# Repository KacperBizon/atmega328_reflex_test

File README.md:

# reflex test

### How to use
- You win by pressing the button on your side faster than your opponent
- To go to the next round press any button for 1s
- Singleplayer - the game finishes with first keypress, multiplayer - both players need to press the keys to finish round 
### Components
- R1 - 10K
- R2-R11 - recommended 3.3k-6.8k
- C1,C2 - 22pF
- C3,C4,C5 - 100nF
- C6 - 10uF

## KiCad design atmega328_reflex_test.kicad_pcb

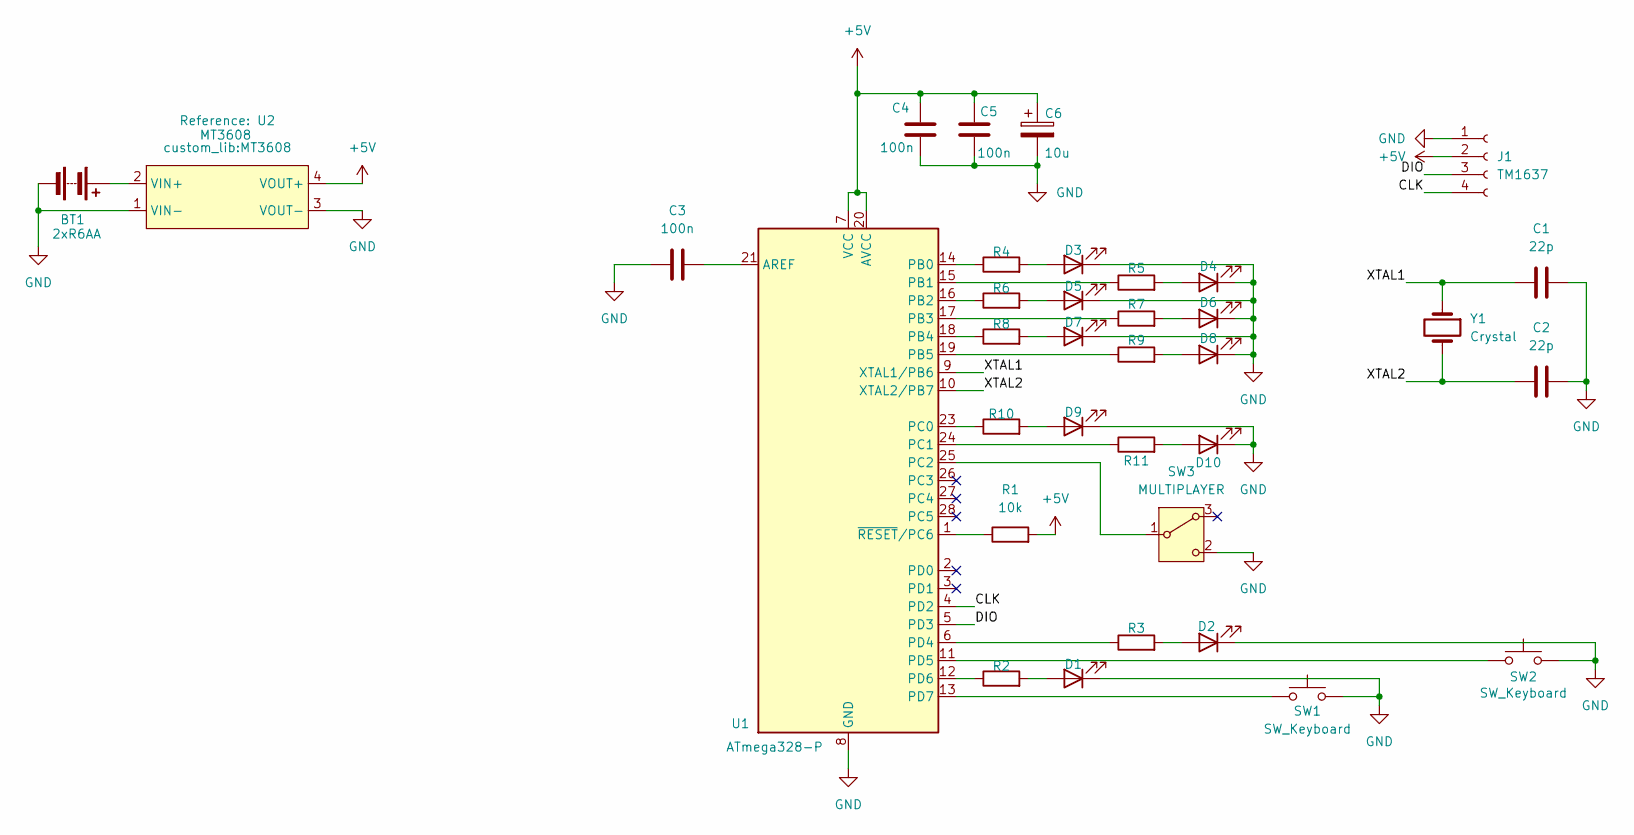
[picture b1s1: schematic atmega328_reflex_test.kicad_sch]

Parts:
BT1: 2xR6AA; 2xAA_holder
C1, C2: 22p; C_Disc_D3.0mm_W1.6mm_P2.50mm
C3, C4, C5: 100n; C_Disc_D4.3mm_W1.9mm_P5.00mm
C6: 10u; CP_Radial_D8.0mm_P3.80mm
D1, D2: LED; LED_D5.0mm
D3, D4, D5, D6, D7, D8, D9, D10: LED; LED_D3.0mm
J1: TM1637; HW069
R1: 10k; R_Axial_DIN0207_L6.3mm_D2.5mm_P7.62mm_Horizontal
R2, R3: 3k3; R_Axial_DIN0207_L6.3mm_D2.5mm_P7.62mm_Horizontal
R4, R5, R6, R7, R8, R9, R10, R11: 5k1; R_Axial_DIN0207_L6.3mm_D2.5mm_P7.62mm_Horizontal
SW1, SW2: SW_Keyboard; SW_Cherry_MX_1.00u_PCB
SW3: MULTIPLAYER; SW_Slide_8.6x3.8x7.0_P2.54mm
U1: ATmega328-P; DIP-28_W7.62mm
U2: MT3608
Y1: Crystal; Crystal_HC49-4H_Vertical

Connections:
+5V: C4.2, C5.2, C6.1, J1.2, R1.2, U1.7 (VCC), U1.20 (AVCC), U2.4 (VOUT+)
/CLK: J1.4, U1.4 (PD2)
/DIO: J1.3, U1.5 (PD3)
/XTAL1: C1.1, U1.9 (XTAL1/PB6), Y1.1
/XTAL2: C2.1, U1.10 (XTAL2/PB7), Y1.2
GND: BT1.2 (-), C1.2, C2.2, C3.1, C4.1, C5.1, C6.2, D1.1 (K), D2.1 (K), D3.1 (K), D4.1 (K), D5.1 (K), D6.1 (K), D7.1 (K), D8.1 (K), D9.1 (K), D10.1 (K), J1.1, SW1.2, SW2.2, SW3.2 (C), U1.8 (GND), U1.22 (GND), U2.1 (VIN-), U2.3 (VOUT-)
unnamed: BT1.1 (+), U2.2 (VIN+)
unnamed: D1.2 (A), R2.2
unnamed: D2.2 (A), R3.2
unnamed: D3.2 (A), R4.2
unnamed: D4.2 (A), R5.2
unnamed: D5.2 (A), R6.2
unnamed: D6.2 (A), R7.2
unnamed: D7.2 (A), R8.2
unnamed: D8.2 (A), R9.2
unnamed: D9.2 (A), R10.2
unnamed: D10.2 (A), R11.2
unnamed: SW3.1 (B), U1.25 (PC2)
unnamed: C3.2, U1.21 (AREF)
unnamed: R4.1, U1.14 (PB0)
unnamed: R5.1, U1.15 (PB1)
unnamed: R6.1, U1.16 (PB2)
unnamed: R7.1, U1.17 (PB3)
unnamed: R8.1, U1.18 (PB4)
unnamed: R9.1, U1.19 (PB5)
unnamed: R10.1, U1.23 (PC0)
unnamed: R11.1, U1.24 (PC1)
unnamed: R3.1, U1.6 (PD4)
unnamed: SW2.1, U1.11 (PD5)
unnamed: R2.1, U1.12 (PD6)
unnamed: SW1.1, U1.13 (PD7)
unnamed: R1.1, U1.1 (~RESET/PC6)

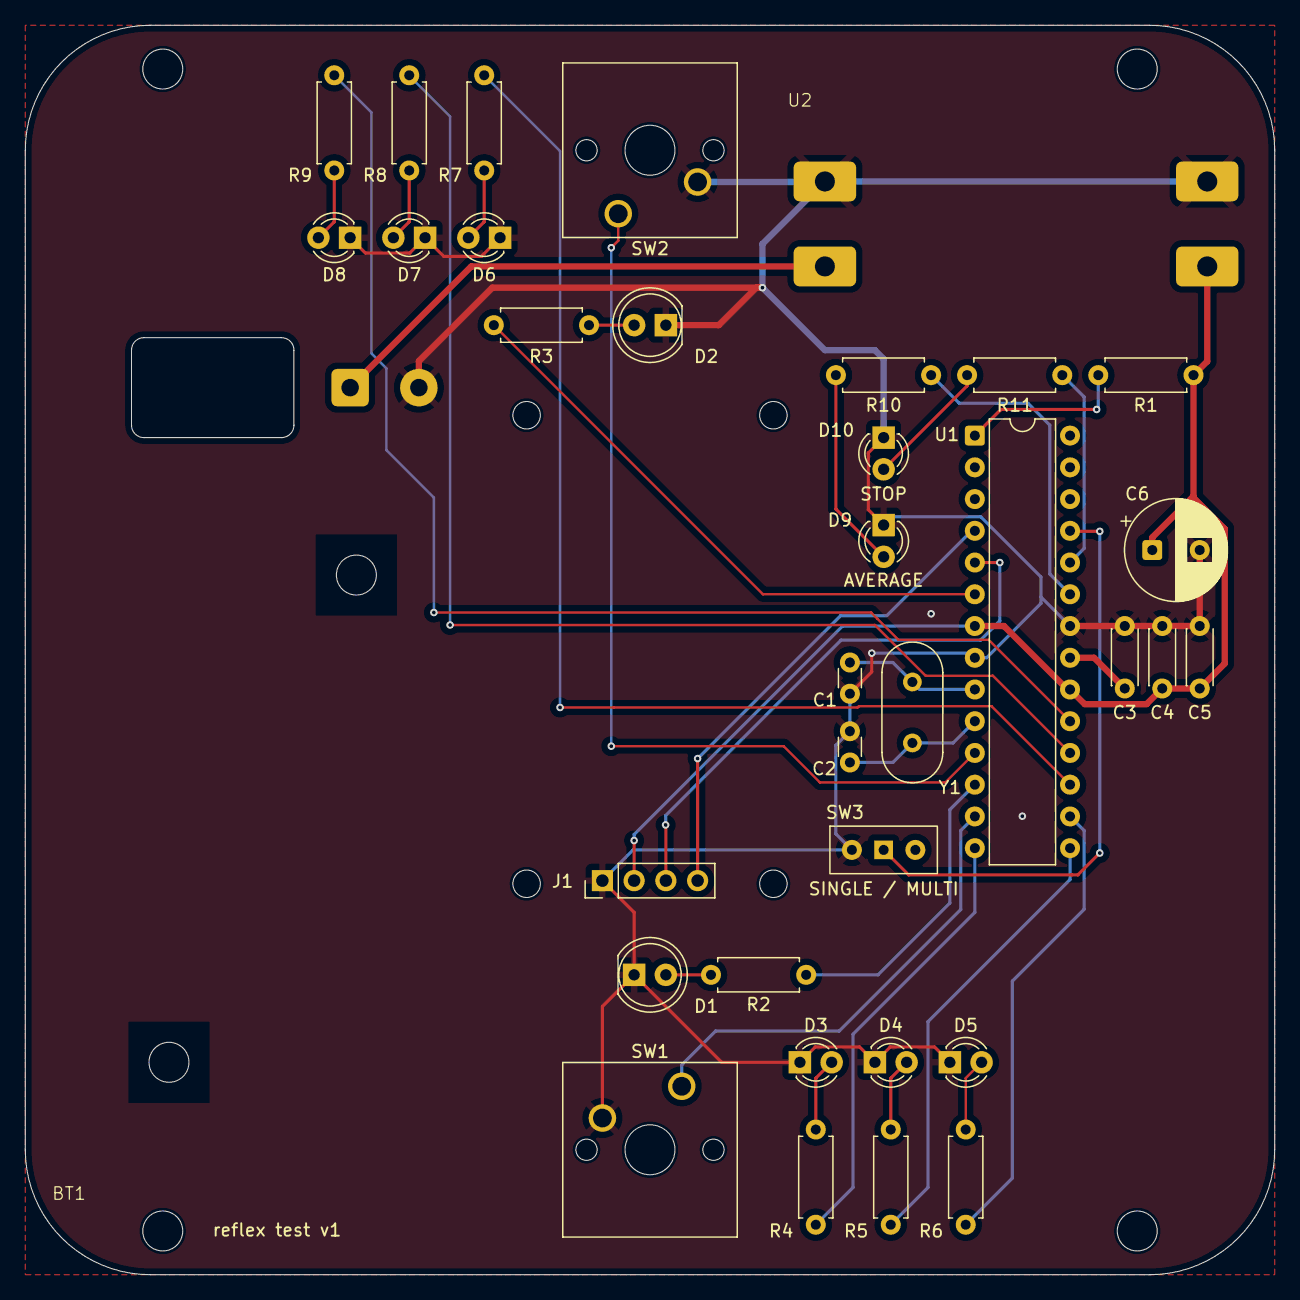
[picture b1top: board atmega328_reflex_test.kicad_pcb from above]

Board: 2 copper layers, 100.0 x 100.0 mm, 39 parts (0 on the bottom side), 32 nets.

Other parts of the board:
MH1, MH2, MH3, MH4: MountingHole_3.2mm_M3_DIN965

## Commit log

2025-11-11 empty nano
2025-11-13 atmega328p minimal
2025-11-13 update files
2025-11-16 shematic without power supply
2025-11-19 add old reflex_ino
2025-11-22 single reaction game
2025-11-22 multiplayer reaction game
2025-11-26 add custom footprints
2025-11-29 added power supply
2025-12-05 finish schematic and general layout
2025-12-10 code reformat, add multiplayer
2025-12-10 multiplayer fix
2025-12-14 pcb components laid out
2025-12-14 initial wiring
    changed pin 4 with pin 7
2025-12-15 version 1 finished
2026-01-10 adjust falsestart delay+safe zone
2026-01-13 Add MIT License
2026-01-13 add readme
2026-01-14 update resistor values
